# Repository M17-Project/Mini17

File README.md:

<div align='center'>

</div>

# Mini17
Mini17 - QRP M17 handheld.

# About
The first handheld to suport M17 was our own [TR-9](https://github.com/M17-Project/TR-9). Unfortunately, the design has a minor flaw in the RF part and is very hard to assemble. After that, we tried modifying various radios with different outcomes. This is our new device - the **Mini17**. It's built around the [CC1200](https://www.ti.com/product/CC1200) RF chip, which does great job at receiving and transmitting M17 signals. The power output is limited to 16dBm (40mW), so it's a QRP radio. The idea is to build a small radio first and then add RF power amplifier stage later. A *Proof of Concept*, if you will. The design could even be extended to a mobile rig in the future.

# Hardware
The RF chip used is CC1200, MCU is STM32F405RGT6. OLED display is the same as in [Module17](https://github.com/M17-Project/Module_17).

# Firmware
[OpenRTX](https://github.com/OpenRTX/OpenRTX) - the Linux of amateur radio!

# Structure
`/Hardware/KiCAD` contains two complete KiCAD projects, one for the mainboard and the other for the HMI<br>
`/MCU/Mini17.ioc` contains the pinout plan for an STM32F405RGT6 MCU (to be used with CubeIDE >=1.10.1)

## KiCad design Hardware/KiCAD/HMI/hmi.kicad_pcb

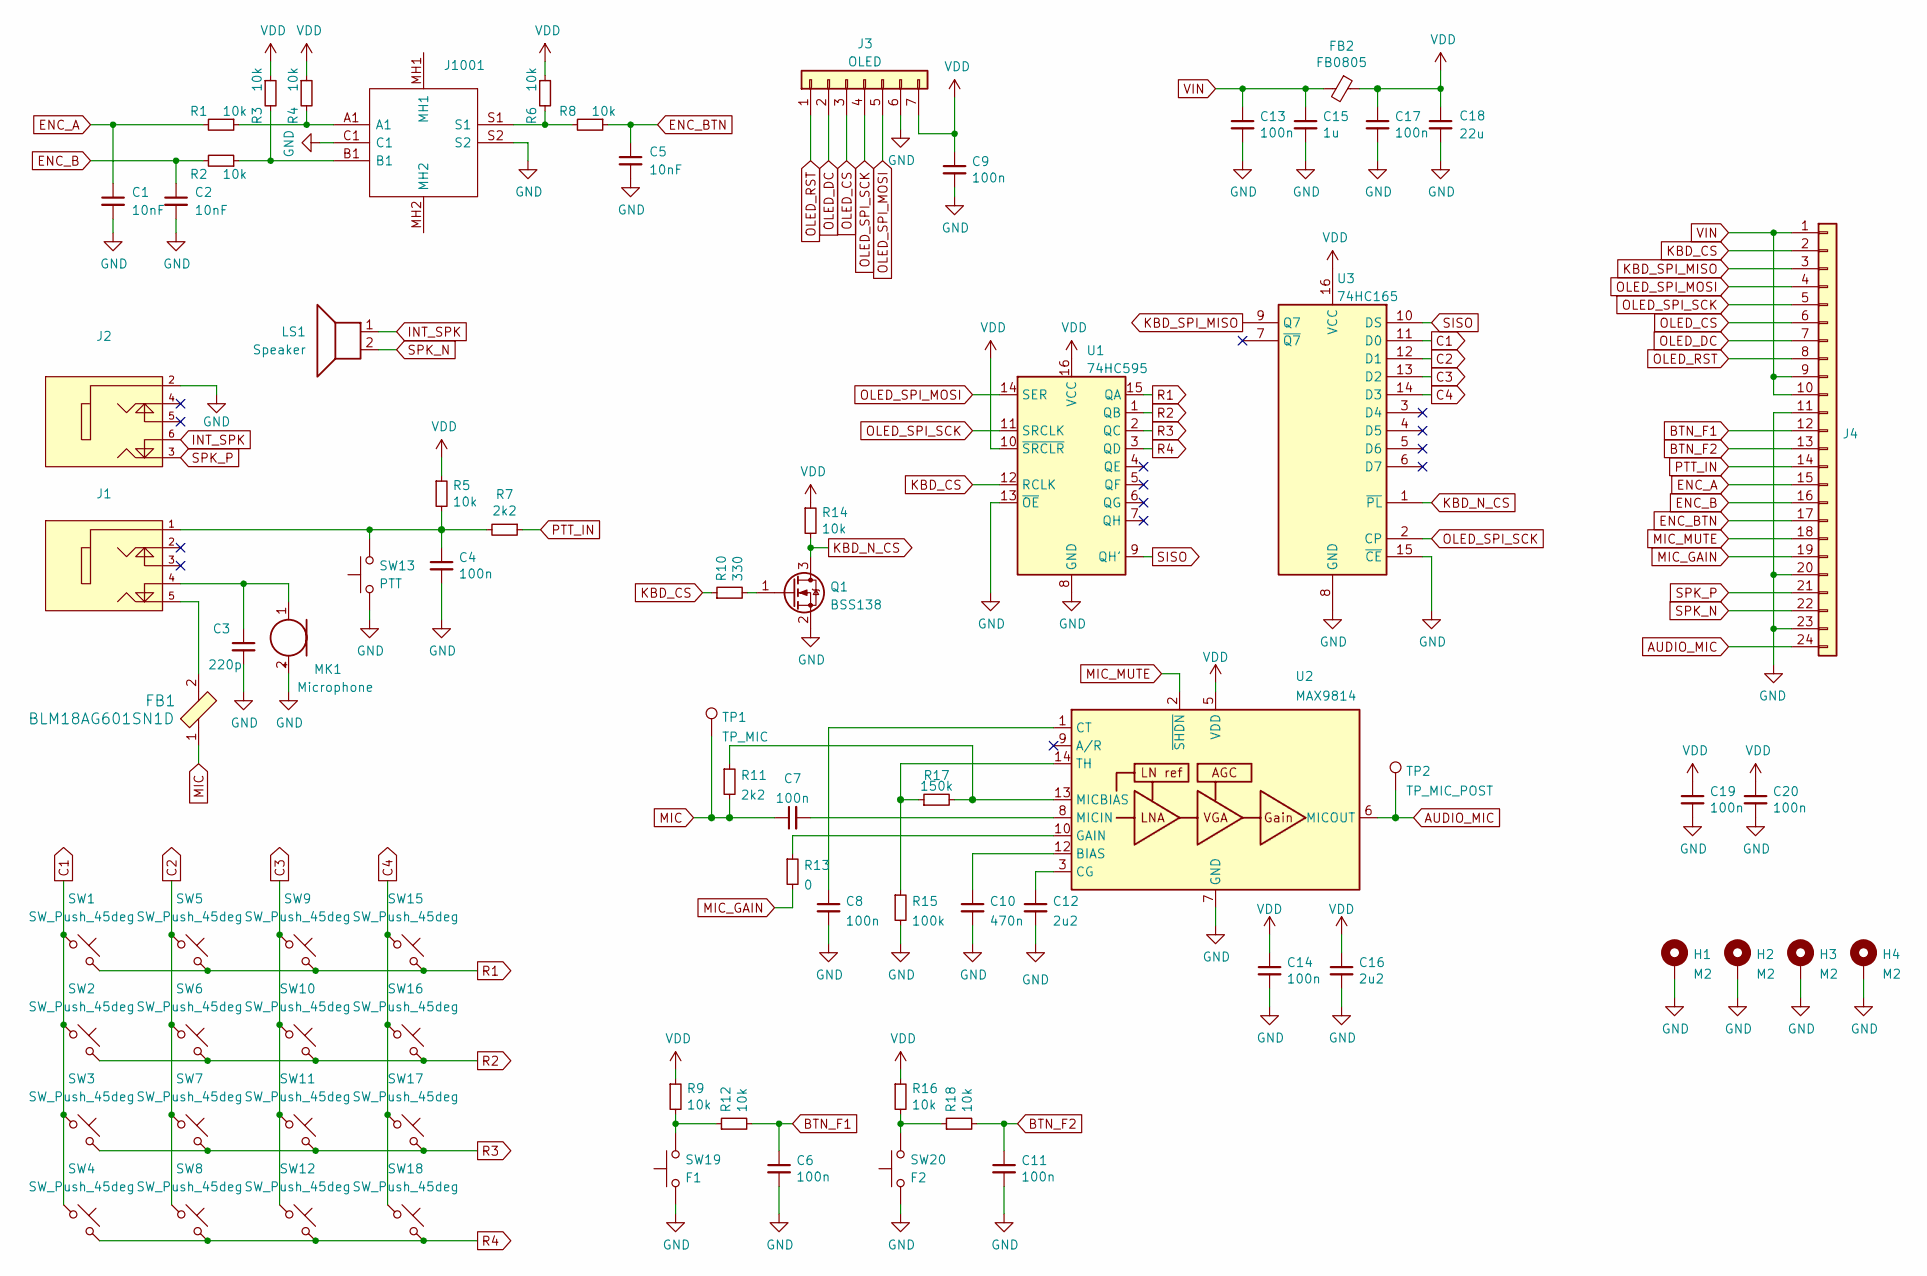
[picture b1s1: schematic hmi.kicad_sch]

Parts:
C1, C2, C5: 10nF; C_0402_1005Metric
C3: 220p; C_0402_1005Metric
C4, C6, C7, C8, C9, C11, C13, C14, C17, C19, C20: 100n; C_0402_1005Metric
C10: 470n; C_0402_1005Metric
C12, C16: 2u2; C_0402_1005Metric
C15: 1u; C_0402_1005Metric
C18: 22u; C_1210_3225Metric
FB1: BLM18AG601SN1D; 0603; MPN BLM18AG601SN1D; Digi-Key_PN 490-1014-1-ND
FB2: FB0805; Fuse_0805_2012Metric
H1, H2, H3, H4: M2; MountingHole_2.2mm_M2_DIN965_Pad
J1, J2, J4: (no value)
J3: OLED; PinHeader_1x07_P2.54mm_Vertical
J1001: Manufacturer_Part_Number ACZ11BR4E-15FA1-20C; Mouser Part Number 490-ACZ11E15FA120C
LS1: Speaker; PinHeader_1x02_P2.54mm_Vertical
MK1: Microphone
Q1: BSS138; SOT-23
R1, R2, R3, R4, R5, R6, R8, R9, R12, R14, R16, R18: 10k; R_0402_1005Metric
R7, R11: 2k2; R_0402_1005Metric
R10: 330; R_0402_1005Metric
R13: 0; R_0402_1005Metric
R15: 100k; R_0402_1005Metric
R17: 150k; R_0402_1005Metric
SW1, SW2, SW3, SW4, SW5, SW6, SW7, SW8, SW9, SW10, SW11, SW12, SW15, SW16, SW17, SW18: SW_Push_45deg; SW_Push_1P1T_NO_CK_KMR2
SW13: PTT; SW_Tactile_SPST_Angled_PTS645Vx31-2LFS
SW19: F1; SW_Tactile_SPST_Angled_PTS645Vx31-2LFS
SW20: F2; SW_Tactile_SPST_Angled_PTS645Vx31-2LFS
TP1: TP_MIC; TestPoint_Pad_D1.0mm
TP2: TP_MIC_POST; TestPoint_Pad_D1.0mm
U1: 74HC595; SOIC-16_3.9x9.9mm_P1.27mm
U2: MAX9814; DFN-14-1EP_3x3mm_P0.4mm_EP1.78x2.35mm
U3: 74HC165; SOIC-16_3.9x9.9mm_P1.27mm

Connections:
AUDIO_MIC: J4.24, TP2.1, U2.6 (MICOUT)
BTN_F1: C6.1, J4.12, R12.2
BTN_F2: C11.1, J4.13, R18.2
C1: SW1.1, SW2.1, SW3.1, SW4.1, U3.11 (D0)
C2: SW5.1, SW6.1, SW7.1, SW8.1, U3.12 (D1)
C3: SW9.1, SW10.1, SW11.1, SW12.1, U3.13 (D2)
C4: SW15.1, SW16.1, SW17.1, SW18.1, U3.14 (D3)
ENC_A: C1.1, J4.15, R1.2
ENC_B: C2.1, J4.16, R2.2
ENC_BTN: C5.1, J4.17, R8.1
GND: C1.2, C2.2, C3.2, C4.2, C5.2, C6.2, C8.2, C9.2, C10.2, C11.2, C12.2, C13.2, C14.2, C15.2, C16.2, C17.2, C18.2, C19.2, C20.2, H1.1, H2.1, H3.1, H4.1, J2.2, J3.6, J4.11, J4.20, J4.23, J1001.C1, J1001.S2, MK1.2 (+), Q1.2 (S), R15.2, SW13.1, SW19.1, SW20.1, U1.8 (GND), U1.13 (~OE), U2.4 (GND), U2.7 (GND), U2.11 (GND), U2.15 (GND), U3.8 (GND), U3.15 (~CE)
INT_SPK: J2.6, LS1.1
KBD_CS: J4.2, R10.1, U1.12 (RCLK)
KBD_N_CS: Q1.3 (D), R14.2, U3.1 (~PL)
KBD_SPI_MISO: J4.3, U3.9 (Q7)
MIC: C7.1, FB1.1, R11.2, TP1.1
MIC_GAIN: J4.19, R13.2
MIC_MUTE: J4.18, U2.2 (~SHDN)
unnamed: C3.1, J1.4, MK1.1 (-)
unnamed: C4.1, J1.1, R5.2, R7.2, SW13.2
unnamed: C7.2, U2.8 (MICIN)
unnamed: C8.1, U2.1 (CT)
unnamed: C10.1, U2.12 (BIAS)
unnamed: C12.1, U2.3 (CG)
unnamed: FB1.2, J1.5
unnamed: Q1.1 (G), R10.2
unnamed: J1001.A1, R1.1, R4.2
unnamed: J1001.B1, R2.1, R3.2
unnamed: J1001.S1, R6.2, R8.2
unnamed: R11.1, R17.2, U2.13 (MICBIAS)
unnamed: R9.2, R12.1, SW19.2
unnamed: R13.1, U2.10 (GAIN)
unnamed: R15.1, R17.1, U2.14 (TH)
unnamed: R16.2, R18.1, SW20.2
OLED_CS: J3.3, J4.6
OLED_DC: J3.2, J4.7
OLED_RST: J3.1, J4.8
OLED_SPI_MOSI: J3.5, J4.4, U1.14 (SER)
OLED_SPI_SCK: J3.4, J4.5, U1.11 (SRCLK), U3.2 (CP)
PTT_IN: J4.14, R7.1
R1: SW1.2, SW5.2, SW9.2, SW15.2, U1.15 (QA)
R2: SW2.2, SW6.2, SW10.2, SW16.2, U1.1 (QB)
R3: SW3.2, SW7.2, SW11.2, SW17.2, U1.2 (QC)
R4: SW4.2, SW8.2, SW12.2, SW18.2, U1.3 (QD)
SISO: U1.9 (QH'), U3.10 (DS)
SPK_N: J4.22, LS1.2
SPK_P: J2.3, J4.21
VDD: C9.1, C14.1, C16.1, C17.1, C18.1, C19.1, C20.1, FB2.1, J3.7, R3.1, R4.1, R5.1, R6.1, R9.1, R14.1, R16.1, U1.10 (~SRCLR), U1.16 (VCC), U2.5 (VDD), U3.16 (VCC)
VIN: C13.1, C15.1, FB2.2, J4.1, J4.9, J4.10

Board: 2 copper layers, 73 parts (0 on the bottom side), 45 nets, no tracks yet.

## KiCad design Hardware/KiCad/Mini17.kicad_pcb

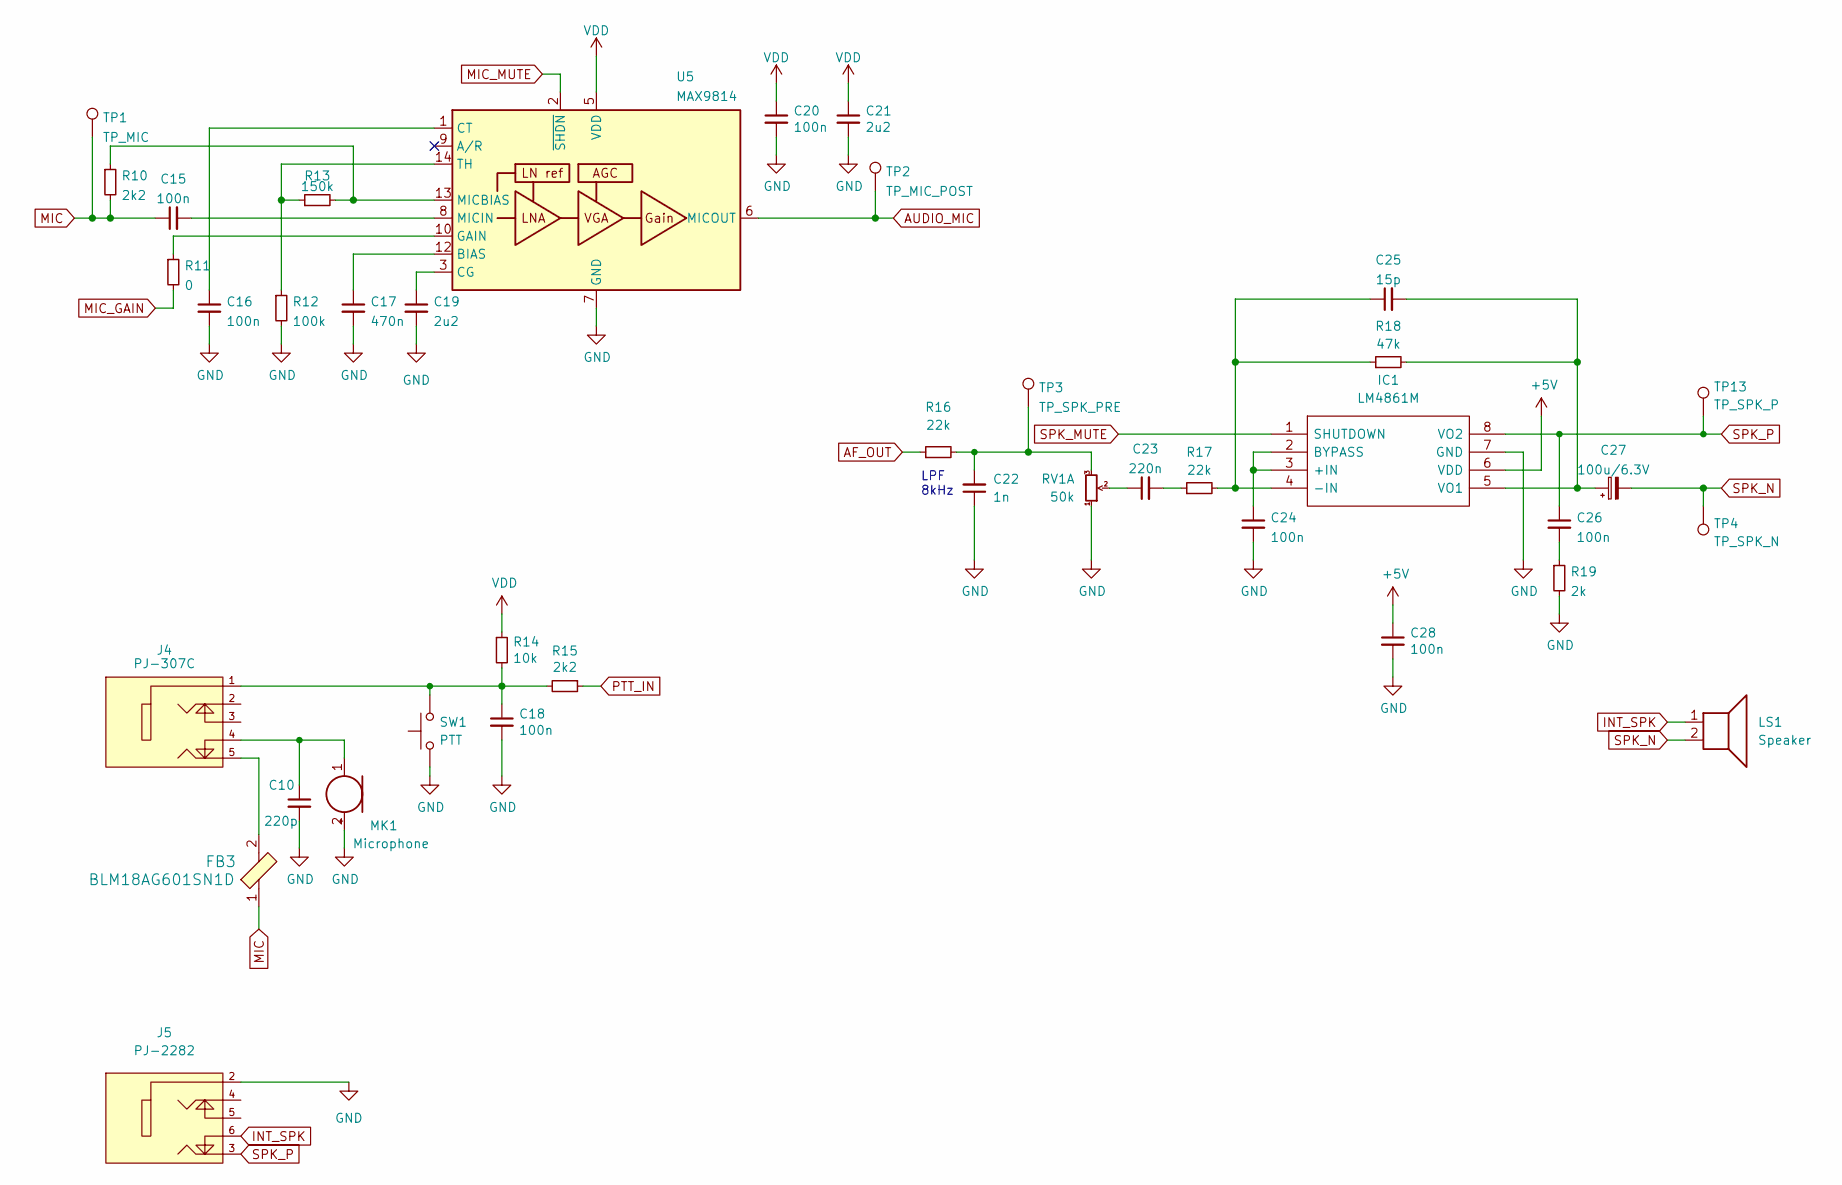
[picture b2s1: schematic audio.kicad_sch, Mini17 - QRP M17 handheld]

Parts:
C10: 220p; C_0402_1005Metric
C15, C16, C18, C20, C24, C26, C28: 100n; C_0402_1005Metric
C17: 470n; C_0402_1005Metric
C19, C21: 2u2; C_0402_1005Metric
C22: 1n; C_0402_1005Metric
C23: 220n; C_0402_1005Metric
C25: 15p; C_0402_1005Metric
C27: 100u/6.3V; C_1206_3216Metric
FB3: BLM18AG601SN1D; 0603; MPN BLM18AG601SN1D; Digi-Key_PN 490-1014-1-ND
IC1: LM4861M; SOIC-8_3.9x4.9mm_P1.27mm; Mouser Part Number 926-LM4861MX/NOPB
J4: PJ-307C
J5: PJ-2282
LS1: Speaker; PinHeader_1x02_P2.54mm_Vertical
MK1: Microphone
R10, R15: 2k2; R_0402_1005Metric
R11: 0; R_0402_1005Metric
R12: 100k; R_0402_1005Metric
R13: 150k; R_0402_1005Metric
R14: 10k; R_0402_1005Metric
R16, R17: 22k; R_0402_1005Metric
R18: 47k; R_0402_1005Metric
R19: 2k; R_0402_1005Metric
RV1: 50k; PTR901
SW1: PTT; SW_Tactile_SPST_Angled_PTS645Vx31-2LFS
TP1: TP_MIC; TestPoint_Pad_D1.0mm
TP2: TP_MIC_POST; TestPoint_Pad_D1.0mm
TP3: TP_SPK_PRE; TestPoint_Pad_D1.0mm
TP4: TP_SPK_N; TestPoint_Pad_D1.0mm
TP13: TP_SPK_P; TestPoint_Pad_D1.0mm
U5: MAX9814; DFN-14-1EP_3x3mm_P0.4mm_EP1.78x2.35mm

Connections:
+5V: C28.1, IC1.6 (VDD); also elsewhere on the board
AF_OUT: R16.1; also elsewhere on the board
AUDIO_MIC: TP2.1, U5.6 (MICOUT); also elsewhere on the board
GND: C10.2, C16.2, C17.2, C18.2, C19.2, C20.2, C21.2, C22.1, C24.2, C28.2, IC1.7 (GND), J5.2, MK1.2 (+), R12.2, R19.2, RV1.1, SW1.1, U5.4 (GND), U5.7 (GND), U5.11 (GND), U5.15 (GND); also elsewhere on the board
INT_SPK: J5.6, LS1.1
MIC: C15.1, FB3.1, R10.2, TP1.1; also elsewhere on the board
MIC_GAIN: R11.2; also elsewhere on the board
MIC_MUTE: U5.2 (~SHDN); also elsewhere on the board
unnamed: C10.1, J4.4, MK1.1 (-)
unnamed: C15.2, U5.8 (MICIN)
unnamed: C16.1, U5.1 (CT)
unnamed: C17.1, U5.12 (BIAS)
unnamed: C18.1, J4.1, R14.2, R15.2, SW1.2
unnamed: C19.1, U5.3 (CG)
unnamed: C22.2, R16.2, RV1.3, TP3.1
unnamed: C23.1, RV1.2
unnamed: C23.2, R17.1
unnamed: C24.1, IC1.2 (BYPASS), IC1.3 (+IN)
unnamed: C25.1, IC1.4 (-IN), R17.2, R18.1
unnamed: C25.2, C27.1, IC1.5 (VO1), R18.2
unnamed: C26.2, R19.1
unnamed 85: FB3.2, J4.5; also elsewhere on the board
unnamed: R10.1, R13.2, U5.13 (MICBIAS)
unnamed: R11.1, U5.10 (GAIN)
unnamed: R12.1, R13.1, U5.14 (TH)
PTT_IN: R15.1; also elsewhere on the board
SPK_MUTE: IC1.1 (SHUTDOWN)
SPK_N: C27.2, LS1.2, TP4.1
SPK_P: C26.1, IC1.8 (VO2), J5.3, TP13.1
VDD: C20.1, C21.1, R14.1, U5.5 (VDD); also elsewhere on the board

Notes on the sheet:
LPF 8kHz

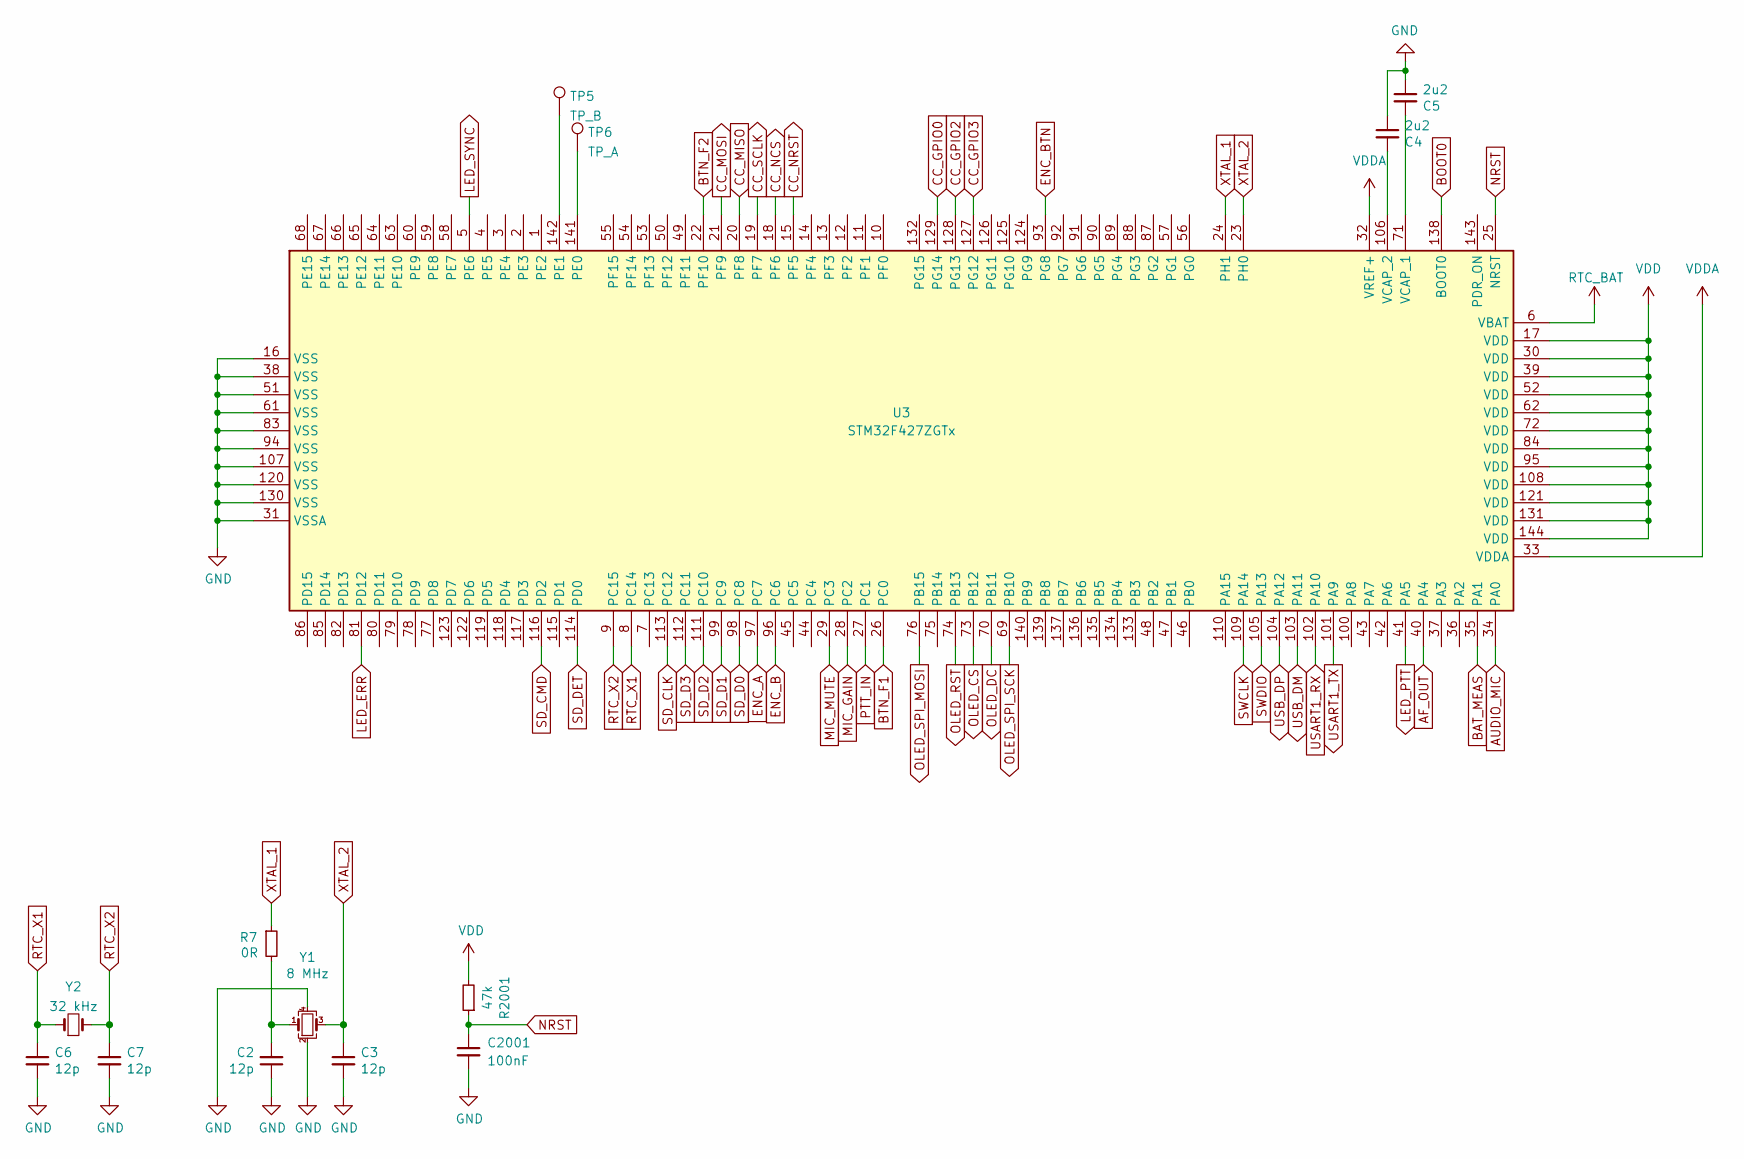
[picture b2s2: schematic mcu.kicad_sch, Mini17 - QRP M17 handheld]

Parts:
C2, C3: 12p; C_0402_1005Metric
C4, C5: 2u2; C_0402_1005Metric
C6, C7: 12p; C_0603
C2001: 100nF; C_0402_1005Metric
R7: 0R; R_0402_1005Metric
R2001: 47k; R_0402_1005Metric
TP5: TP_B; TestPoint_Pad_D1.0mm
TP6: TP_A; TestPoint_Pad_D1.0mm
U3: STM32F427ZGTx; LQFP-144_20x20mm_P0.5mm
Y1: 8 MHz; Crystal_SMD_3225-4Pin_3.2x2.5mm
Y2: 32 kHz; Crystal_SMD_MicroCrystal_CC8V-T1A-2Pin_2.0x1.2mm

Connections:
AF_OUT: U3.40 (PA4); also elsewhere on the board
AUDIO_MIC: U3.34 (PA0); also elsewhere on the board
BAT_MEAS: U3.35 (PA1); also elsewhere on the board
BOOT0: U3.138 (BOOT0); also elsewhere on the board
BTN_F1: U3.26 (PC0); also elsewhere on the board
BTN_F2: U3.22 (PF10); also elsewhere on the board
CC_GPIO0: U3.129 (PG14); also elsewhere on the board
CC_GPIO2: U3.128 (PG13); also elsewhere on the board
CC_GPIO3: U3.127 (PG12); also elsewhere on the board
CC_MISO: U3.20 (PF8); also elsewhere on the board
CC_MOSI: U3.21 (PF9); also elsewhere on the board
CC_NCS: U3.18 (PF6); also elsewhere on the board
CC_NRST: U3.15 (PF5); also elsewhere on the board
CC_SCLK: U3.19 (PF7); also elsewhere on the board
ENC_A: U3.97 (PC7); also elsewhere on the board
ENC_B: U3.96 (PC6); also elsewhere on the board
ENC_BTN: U3.93 (PG8); also elsewhere on the board
GND: C2.1, C3.2, C4.1, C5.1, C6.2, C7.2, C2001.2, U3.16 (VSS), U3.31 (VSSA), U3.38 (VSS), U3.51 (VSS), U3.61 (VSS), U3.83 (VSS), U3.94 (VSS), U3.107 (VSS), U3.120 (VSS), U3.130 (VSS), Y1.2, Y1.4; also elsewhere on the board
LED_ERR: U3.81 (PD12)
LED_PTT: U3.41 (PA5)
LED_SYNC: U3.5 (PE6)
MIC_GAIN: U3.28 (PC2); also elsewhere on the board
MIC_MUTE: U3.29 (PC3); also elsewhere on the board
NRST: C2001.1, R2001.1, U3.25 (NRST); also elsewhere on the board
unnamed: C2.2, R7.2, Y1.1
unnamed: C4.2, U3.106 (VCAP_2)
unnamed: C5.2, U3.71 (VCAP_1)
unnamed: TP5.1, U3.142 (PE1)
unnamed: TP6.1, U3.141 (PE0)
OLED_CS: U3.73 (PB12); also elsewhere on the board
OLED_DC: U3.70 (PB11)
OLED_RST: U3.74 (PB13); also elsewhere on the board
OLED_SPI_MOSI: U3.76 (PB15); also elsewhere on the board
OLED_SPI_SCK: U3.69 (PB10); also elsewhere on the board
PTT_IN: U3.27 (PC1); also elsewhere on the board
RTC_X1: C6.1, U3.8 (PC14), Y2.1
RTC_X2: C7.1, U3.9 (PC15), Y2.2
SD_CLK: U3.113 (PC12); also elsewhere on the board
SD_CMD: U3.116 (PD2); also elsewhere on the board
SD_D0: U3.98 (PC8); also elsewhere on the board
SD_D1: U3.99 (PC9); also elsewhere on the board
SD_D2: U3.111 (PC10); also elsewhere on the board
SD_D3: U3.112 (PC11); also elsewhere on the board
SD_DET: U3.114 (PD0)
SWCLK: U3.109 (PA14); also elsewhere on the board
SWDIO: U3.105 (PA13); also elsewhere on the board
USART1_RX: U3.102 (PA10); also elsewhere on the board
USART1_TX: U3.101 (PA9); also elsewhere on the board
USB_DM: U3.103 (PA11); also elsewhere on the board
USB_DP: U3.104 (PA12); also elsewhere on the board
VDD: R2001.2, U3.17 (VDD), U3.30 (VDD), U3.39 (VDD), U3.52 (VDD), U3.62 (VDD), U3.72 (VDD), U3.84 (VDD), U3.95 (VDD), U3.108 (VDD), U3.121 (VDD), U3.131 (VDD), U3.144 (VDD); also elsewhere on the board
VDDA: U3.32 (VREF+), U3.33 (VDDA); also elsewhere on the board
XTAL_1: R7.1, U3.24 (PH1)
XTAL_2: C3.1, U3.23 (PH0), Y1.3

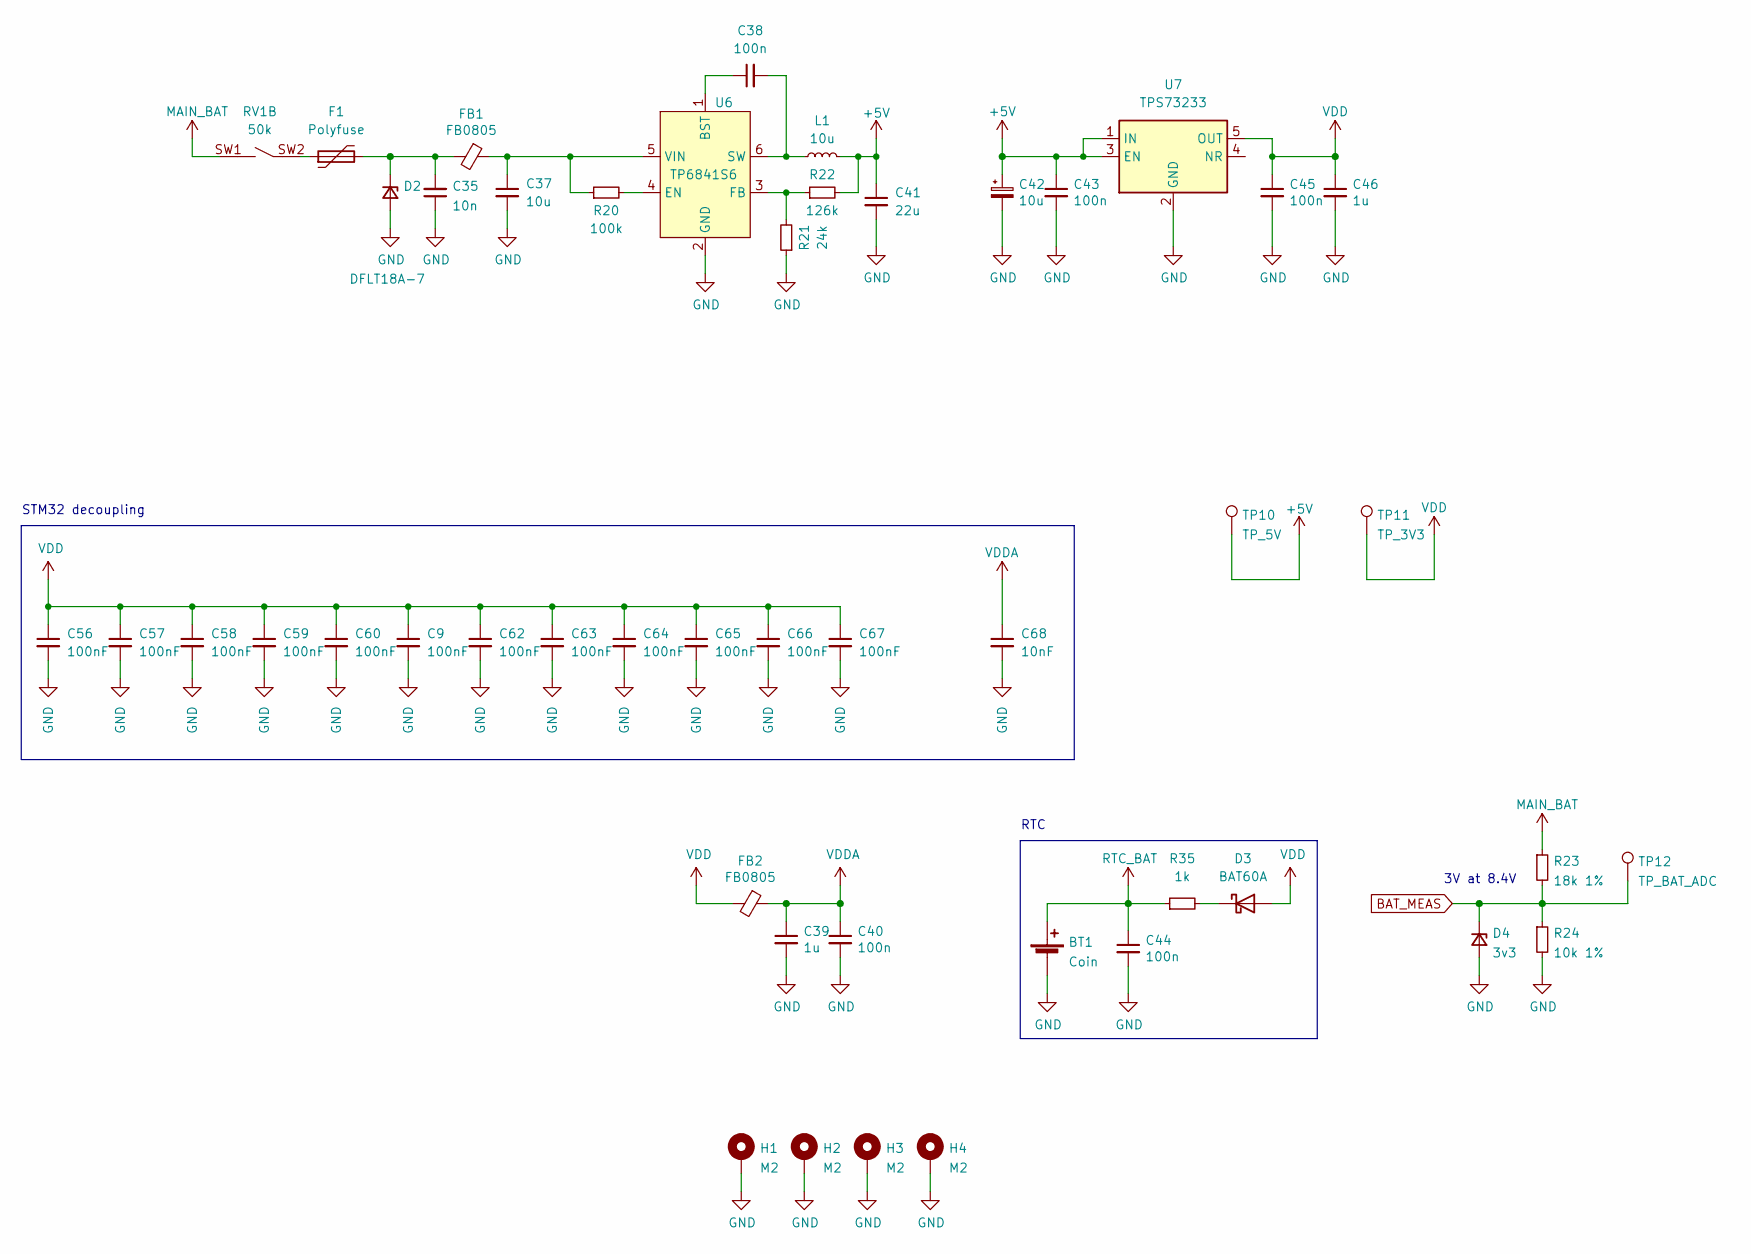
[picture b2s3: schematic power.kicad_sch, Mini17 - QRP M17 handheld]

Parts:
BT1: Coin; BatteryHolder_Keystone_3000_1x12mm
C9, C56, C57, C58, C59, C60, C62, C63, C64, C65, C66, C67: 100nF; C_0402_1005Metric
C35: 10n; C_0402_1005Metric
C37: 10u; C_0603_1608Metric
C38, C40, C43, C45: 100n; C_0402_1005Metric
C39, C46: 1u; C_0402_1005Metric
C41: 22u; C_1210_3225Metric
C42: 10u; CP_EIA-3216-18_Kemet-A
C44: 100n; C_0603
C68: 10nF; C_0402_1005Metric
D2: DFLT18A-7; D_SOD-128
D3: BAT60A; D_SOD-323
D4: 3v3; D_SOD-523
F1: Polyfuse; Fuse_0805_2012Metric
FB1, FB2: FB0805; Fuse_0805_2012Metric
H1, H2, H3, H4: M2; MountingHole_2.2mm_M2_DIN965_Pad
L1: 10u; L_Vishay_IHLP-2525; Partno IHLP2525CZER100M01
R20: 100k; R_0402_1005Metric
R21: 24k; R_0402_1005Metric
R22: 126k; R_0402_1005Metric
R23: 18k 1%; R_0402_1005Metric
R24: 10k 1%; R_0402_1005Metric
R35: 1k; R_0402_1005Metric
RV1: 50k; PTR901
TP10: TP_5V; TestPoint_Pad_D1.0mm
TP11: TP_3V3; TestPoint_Pad_D1.0mm
TP12: TP_BAT_ADC; TestPoint_Pad_D1.0mm
U6: TP6841S6; SOT-23-6
U7: TPS73233; SOT-23-5

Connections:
+5V: C41.1, C42.1, C43.1, L1.1, R22.2, TP10.1, U7.1 (IN), U7.3 (EN); also elsewhere on the board
BAT_MEAS: D4.1 (K), R23.2, R24.1, TP12.1; also elsewhere on the board
GND: BT1.2 (-), C9.2, C35.1, C37.2, C39.2, C40.2, C41.2, C42.2, C43.2, C44.2, C45.2, C46.2, C56.2, C57.2, C58.2, C59.2, C60.2, C62.2, C63.2, C64.2, C65.2, C66.2, C67.2, C68.2, D2.2 (A), D4.2 (A), H1.1, H2.1, H3.1, H4.1, R21.1, R24.2, U6.2 (GND), U7.2 (GND); also elsewhere on the board
unnamed: C35.2, D2.1 (K), F1.2, FB1.2
unnamed: C37.1, FB1.1, R20.1, U6.5 (VIN)
unnamed: C38.1, U6.1 (BST)
unnamed: C38.2, L1.2, U6.6 (SW)
unnamed: D3.1 (K), R35.2
unnamed: F1.1, RV1.SW2 (SW)
unnamed: R20.2, U6.4 (EN)
unnamed: R21.2, R22.1, U6.3 (FB)
VDD: C9.1, C45.1, C46.1, C56.1, C57.1, C58.1, C59.1, C60.1, C62.1, C63.1, C64.1, C65.1, C66.1, C67.1, D3.2 (A), FB2.2, TP11.1, U7.5 (OUT); also elsewhere on the board
VDDA: C39.1, C40.1, C68.1, FB2.1; also elsewhere on the board

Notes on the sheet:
3V at 8.4V
RTC
STM32 decoupling

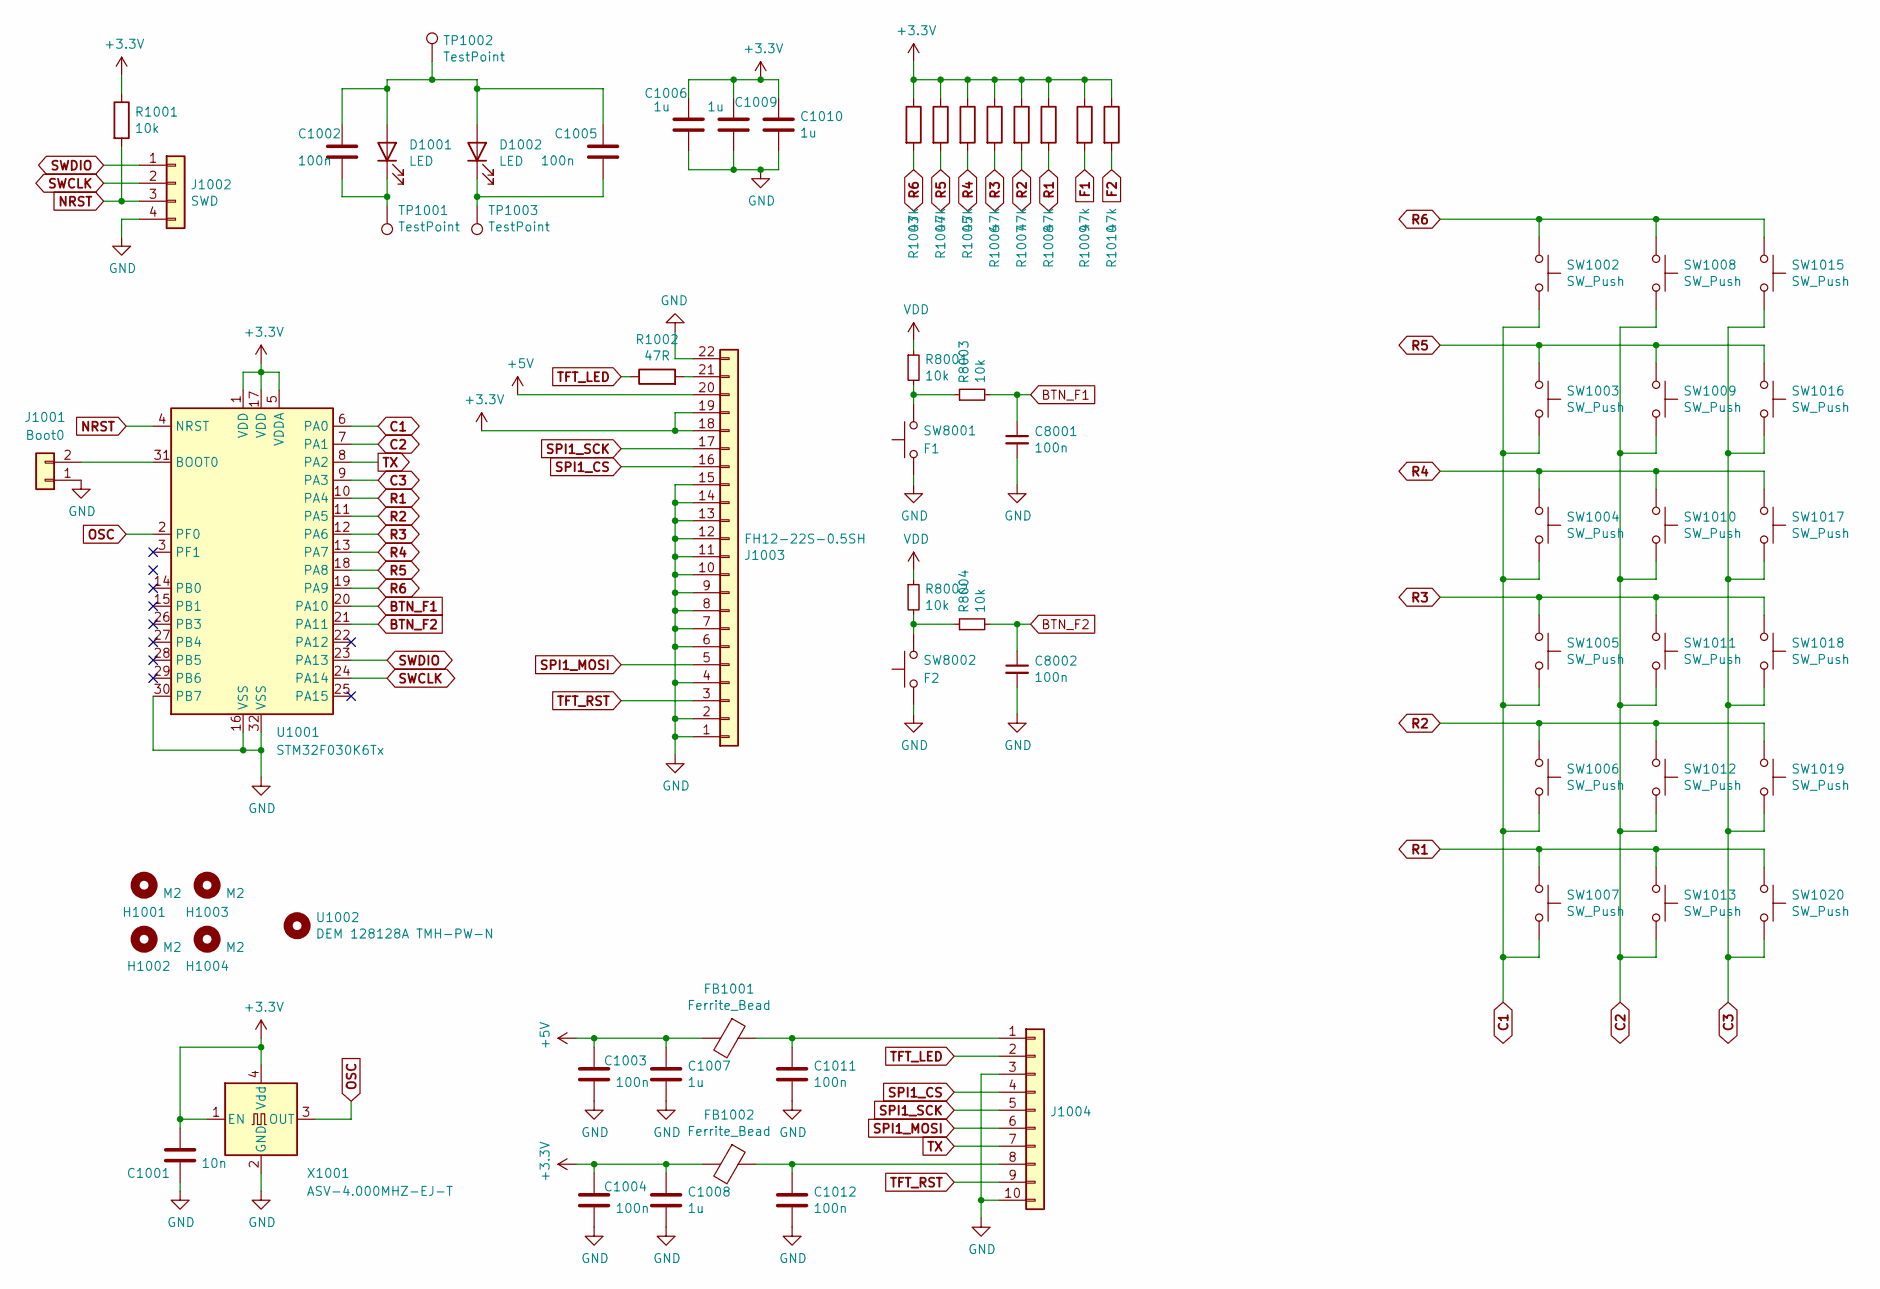
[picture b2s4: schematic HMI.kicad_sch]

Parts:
C1001: 10n; C_0603_1608Metric
C1002, C1003, C1004, C1005, C1011, C1012: 100n; C_0603_1608Metric
C1006, C1007, C1008, C1009, C1010: 1u; C_0603_1608Metric
C8001, C8002: 100n; C_0402_1005Metric
D1001, D1002: LED; D_0603_1608Metric
FB1001, FB1002: Ferrite_Bead; L_0603_1608Metric
H1001, H1002, H1003, H1004: M2; MountingHole_2.2mm_M2_ISO14580_Pad
J1001: Boot0; PinHeader_1x02_P2.54mm_Vertical
J1002: SWD; PinHeader_1x04_P1.27mm_Vertical
J1003: FH12-22S-0.5SH; Hirose_FH12-22S-0.5SH_1x22-1MP_P0.50mm_Horizontal
J1004: Hirose_FH12-10S-0.5SH_1x10-1MP_P0.50mm_Horizontal
R1001: 10k; R_0603_1608Metric
R1002: 47R; R_0603_1608Metric
R1003, R1004, R1005, R1006, R1007, R1008, R1009, R1010: 47k; R_0603_1608Metric
R8001, R8002, R8003, R8004: 10k; R_0402_1005Metric
SW1002, SW1003, SW1004, SW1005, SW1006, SW1007, SW1008, SW1009, SW1010, SW1011, SW1012, SW1013, SW1015, SW1016, SW1017, SW1018, SW1019, SW1020: SW_Push; SW_Push_1P1T_NO_CK_KMR2
SW8001: F1; SW_Tactile_SPST_Angled_PTS645Vx31-2LFS
SW8002: F2; SW_Tactile_SPST_Angled_PTS645Vx31-2LFS
TP1001, TP1002, TP1003: TestPoint; TestPoint_Pad_2.0x2.0mm
U1001: STM32F030K6Tx; LQFP-32_7x7mm_P0.8mm
U1002: DEM 128128A TMH-PW-N; DEM_128128A_TMH-PW-N
X1001: ASV-4.000MHZ-EJ-T; Oscillator_SMD_Abracon_ASV-4Pin_7.0x5.1mm

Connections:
+3V3: C1001.1, C1004.1, C1006.1, C1008.1, C1009.1, C1010.1, FB1002.2, J1003.18, J1003.19, R1001.1, R1003.1, R1004.1, R1005.1, R1006.1, R1007.1, R1008.1, R1009.1, R1010.1, U1001.1 (VDD), U1001.5 (VDDA), U1001.17 (VDD), X1001.1 (EN), X1001.4 (Vdd)
+5V: C1003.1, C1007.1, FB1001.2, J1003.20; also elsewhere on the board
BTN_F1: C8001.1, R8003.2, U1001.20 (PA10); also elsewhere on the board
BTN_F2: C8002.1, R8004.2, U1001.21 (PA11); also elsewhere on the board
C1: SW1002.2, SW1003.2, SW1004.2, SW1005.2, SW1006.2, SW1007.2, U1001.6 (PA0)
C2: SW1008.2, SW1009.2, SW1010.2, SW1011.2, SW1012.2, SW1013.2, U1001.7 (PA1)
C3: SW1015.2, SW1016.2, SW1017.2, SW1018.2, SW1019.2, SW1020.2, U1001.9 (PA3)
F1: R1009.2
F2: R1010.2
GND: C1001.2, C1003.2, C1004.2, C1006.2, C1007.2, C1008.2, C1009.2, C1010.2, C1011.2, C1012.2, C8001.2, C8002.2, J1001.1, J1002.4, J1003.1, J1003.2, J1003.4, J1003.6, J1003.7, J1003.8, J1003.9, J1003.10, J1003.11, J1003.12, J1003.13, J1003.14, J1003.15, J1003.22, J1004.3, J1004.10, SW8001.1, SW8002.1, U1001.16 (VSS), U1001.30 (PB7), U1001.32 (VSS), X1001.2 (GND); also elsewhere on the board
NRST: J1002.3, R1001.2, U1001.4 (NRST); also elsewhere on the board
unnamed: C1002.1, C1005.1, D1001.2 (A), D1002.2 (A), TP1002.1
unnamed: C1002.2, D1001.1 (K), TP1001.1
unnamed: C1005.2, D1002.1 (K), TP1003.1
unnamed: C1011.1, FB1001.1, J1004.1
unnamed: C1012.1, FB1002.1, J1004.8
unnamed: J1001.2, U1001.31 (BOOT0)
unnamed: J1003.21, R1002.2
unnamed: R8001.2, R8003.1, SW8001.2
unnamed: R8002.2, R8004.1, SW8002.2
OSC: U1001.2 (PF0), X1001.3 (OUT)
R1: R1008.2, SW1007.1, SW1013.1, SW1020.1, U1001.10 (PA4)
R2: R1007.2, SW1006.1, SW1012.1, SW1019.1, U1001.11 (PA5)
R3: R1006.2, SW1005.1, SW1011.1, SW1018.1, U1001.12 (PA6)
R4: R1005.2, SW1004.1, SW1010.1, SW1017.1, U1001.13 (PA7)
R5: R1004.2, SW1003.1, SW1009.1, SW1016.1, U1001.18 (PA8)
R6: R1003.2, SW1002.1, SW1008.1, SW1015.1, U1001.19 (PA9)
SPI1_CS: J1003.16, J1004.4
SPI1_MOSI: J1003.5, J1004.6
SPI1_SCK: J1003.17, J1004.5
SWCLK: J1002.2, U1001.24 (PA14); also elsewhere on the board
SWDIO: J1002.1, U1001.23 (PA13); also elsewhere on the board
TFT_LED: J1004.2, R1002.1; also elsewhere on the board
TFT_RST: J1003.3, J1004.9
TX: J1004.7, U1001.8 (PA2)
VDD: R8001.1, R8002.1; also elsewhere on the board
